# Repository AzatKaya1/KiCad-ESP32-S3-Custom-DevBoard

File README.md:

<div align="center">

# ⚡ ESP32-S3 Custom Development Board

</div>
<div align="center">

<br/>

**A production-grade, 4-layer PCB development board built around the ESP32-S3-WROOM-1 module.**  
Designed for signal integrity, RF performance, and professional-grade hardware standards.

<br/>

</div>

## 📋 Table of Contents

- [Overview](#-overview)
- [Key Features](#-key-features)
- [Technical Specifications](#-technical-specifications)
- [Advanced Hardware Design](#-advanced-hardware-design)
- [PCB Layer Stackup](#-pcb-layer-stackup)
- [Pinout & Peripherals](#-pinout--peripherals)
- [Repository Structure](#-repository-structure)
- [Manufacturing](#-manufacturing)

## 🔍 Overview

This project is an advanced, **production-ready development board** based on the **ESP32-S3-WROOM-1** module. It was designed with a focus on:

- ✅ **Signal Integrity** — Controlled impedance traces, optimized return paths
- ✅ **Power Stability** — Low-noise LDO regulation with proper decoupling
- ✅ **RF Performance** — Dedicated keep-out zone under the module antenna
- ✅ **Professional Standards** — 4-layer stackup, differential pair routing

This board is suitable for makers, engineers, and students who want a reliable ESP32-S3 platform for IoT, wireless communication, sensor integration, or embedded systems development.

## ✨ Key Features

| Feature | Detail |
|---|---|
| 🧠 MCU | ESP32-S3-WROOM-1 — Dual-core Xtensa LX7, Wi-Fi 4 & BLE 5.0 |
| ⚡ USB | Native USB-C for programming and power |
| 🔋 Power | 5V input → 3.3V via AMS1117-3.3 LDO |
| 📡 RF | Keep-out zone for optimized antenna performance |
| 📐 PCB | 4-layer stackup for reduced EMI |
| 🔌 Headers | UART, I2C, SPI — fully broken out |
| 📊 ADC | 2× dedicated analog input channels |
| 🔴 LEDs | Power LED (D1) + User-programmable LED (D2) |
| 🔘 Buttons | RESET (EN) + BOOT (GPIO0) |
| 🧪 Test Points | 5V, 3.3V, GND, TX, RX (TP1–TP5) |

## 🛠 Technical Specifications

| Parameter | Value |
|---|---|
| Microcontroller | ESP32-S3-WROOM-1 |
| CPU | Dual-core Xtensa LX7 @ up to 240 MHz |
| Wireless | Wi-Fi 802.11 b/g/n (2.4 GHz) + BLE 5.0 |
| Flash | Built-in (varies by module variant) |
| Input Voltage | 5V DC via USB-C |
| Operating Voltage | 3.3V (regulated via AMS1117-3.3) |
| PCB Layers | 4 (Signal / GND / Power / Signal) |
| PCB Tool | KiCad 9.0 |
| USB Interface | Native USB (D+/D- differential pair) |
| Programming | USB-C (native), UART via test points |

## 🔬 Advanced Hardware Design

### 1️⃣ 4-Layer PCB & Signal Integrity

The board uses a **4-layer stackup** to deliver superior electrical performance.

By using dedicated internal planes for **GND** and **3.3V**, electromagnetic interference (EMI) is significantly reduced, and power distribution is stabilized across the entire board.

### 2️⃣ Differential Pair Routing (USB D+/D-)

The USB-C data lines are routed as **90-ohm controlled impedance differential pairs**:

- Matched trace lengths for minimal skew
- Consistent spacing to maintain target impedance
- Prevents signal reflection and ensures error-free high-speed data transmission

### 3️⃣ RF Keep-Out Zone

A dedicated **RF Keep-Out Zone** is defined beneath the ESP32-S3-WROOM-1 antenna region:

- No copper, traces, or components on **any layer** in this region
- Maximizes Wi-Fi and Bluetooth range
- Minimizes signal attenuation and multipath interference

### 4️⃣ Power Design — AMS1117-3.3 LDO

The **AMS1117-3.3** was chosen for its:

- Low dropout voltage (~1.2V typical)
- 800mA output current capability
- Excellent noise performance for RF applications
- Wide availability and low cost for prototyping

> ⚠️ **Note:** For battery-powered or low-power designs, consider a more efficient LDO (e.g., MIC5219 or TPS7A20).

### 5️⃣ Decoupling & Bypass Capacitors

- 100nF ceramic capacitors placed close to each power pin of the ESP32-S3 module
- Bulk capacitance at the LDO output for transient response
- Ferrite bead filtering on power input

## 📐 PCB Layer Stackup

| Layer | Type | Description |
|---|---|---|
| Layer 1 (Top) | Signal | Components, USB, buttons, LEDs |
| Layer 2 | GND Plane | Solid ground pour — EMI shield & return path |
| Layer 3 | Power Plane | Solid 3.3V pour — stable power delivery |
| Layer 4 (Bottom) | Signal | Additional routing |

## 🔌 Pinout & Peripherals

| Header | Signals |
|---|---|
| UART | TX, RX, GND, 3.3V |
| I2C | SDA, SCL, GND, 3.3V |
| SPI | MOSI, MISO, SCK, CS, GND, 3.3V |
| ADC | ADC_CH1, ADC_CH2, GND |
| GPIO | Spare GPIO pins for custom expansion |
| Test Points | TP1 = 5V · TP2 = 3.3V · TP3 = GND · TP4 = TX · TP5 = RX |

## 📂 Repository Structure

| Folder / File | Description |
|---|---|
| `Hardware/` | KiCad 9.0 project files (`.kicad_pcb`, `.kicad_sch`, `.kicad_pro`) |
| `Manufacturing/` | Production-ready Gerber, Drill, and POS files |
| `Images/` | High-quality 3D renders |
| `.gitignore` | Git ignore rules |
| `LICENSE` | MIT License |
| `README.md` | This file |

## 🏭 Manufacturing

The `/Manufacturing` folder contains all files needed for PCB fabrication, compatible with major manufacturers:

| Service | Notes |
|---|---|
| [JLCPCB](https://jlcpcb.com) | Recommended — affordable 4-layer PCBs |
| [PCBWay](https://www.pcbway.com) | Good quality, various finish options |
| [OSH Park](https://oshpark.com) | US-based, ENIG finish standard |

**Recommended fab settings:**

| Parameter | Value |
|---|---|
| Layers | 4 |
| PCB Color | Black (recommended) |
| Surface Finish | HASL or ENIG |
| Board Thickness | 1.6mm |
| Copper Weight | 1oz outer / 0.5oz inner |
| Min Trace/Space | 0.15mm |
| Min Hole Size | 0.3mm |

---

<div align="center">

**Designed with  by [Azat KAYA](https://www.linkedin.com/in/azatkaya1/)**

*If this project helped you, consider giving it a ⭐ on GitHub!*

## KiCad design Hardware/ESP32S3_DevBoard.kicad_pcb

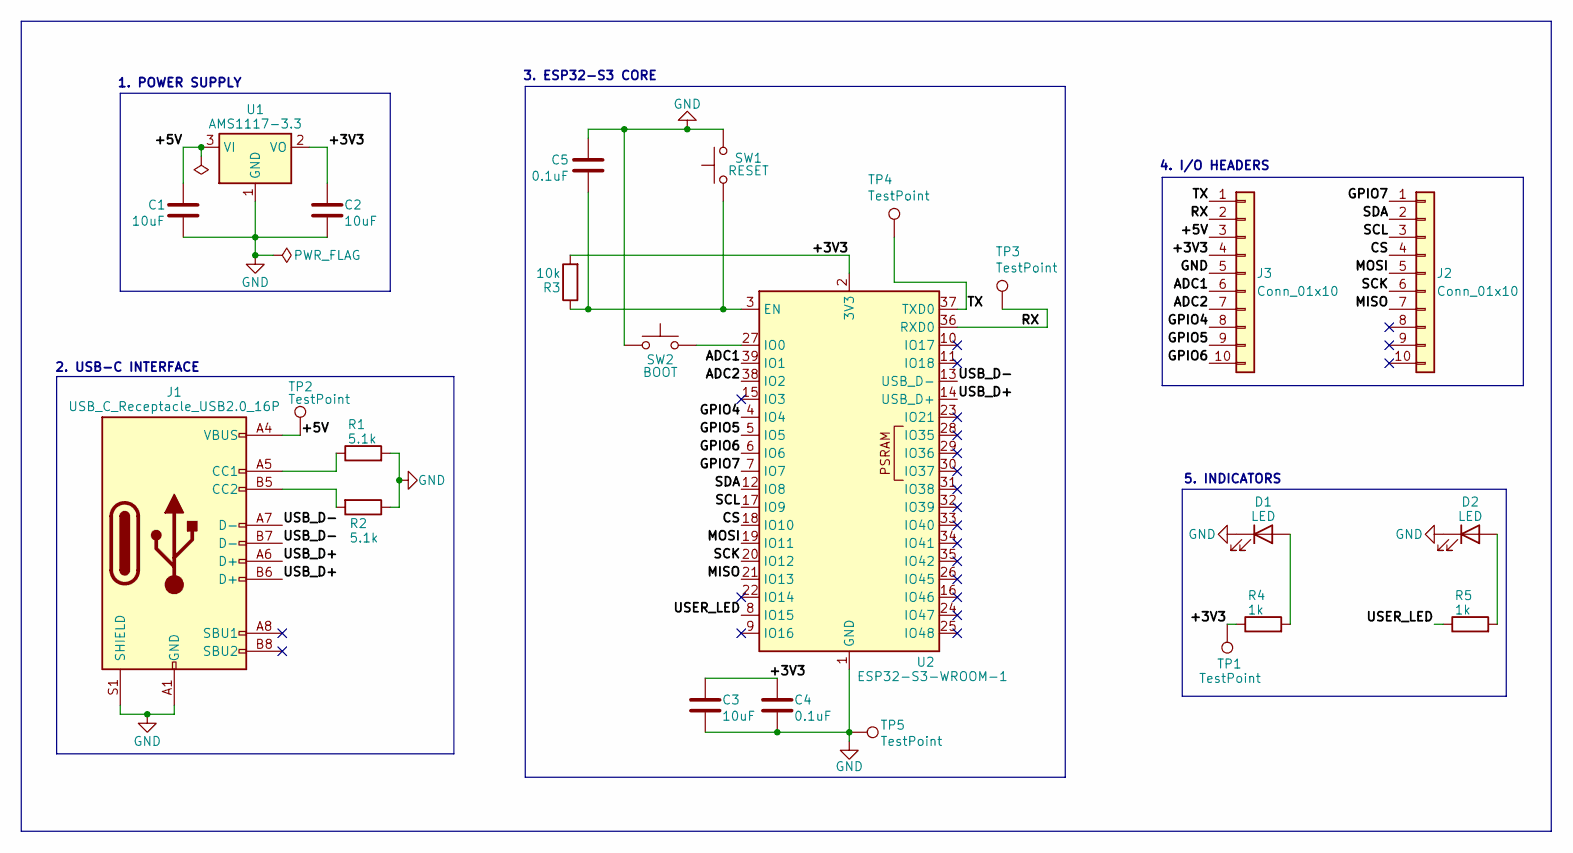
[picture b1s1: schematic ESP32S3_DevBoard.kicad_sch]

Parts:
C1, C2, C3: 10uF; C_0805_2012Metric
C4, C5: 0.1uF; C_0805_2012Metric
D1, D2: LED; LED_0805_2012Metric
J1: USB_C_Receptacle_USB2.0_16P; USB_C_Receptacle_HRO_TYPE-C-31-M-12
J2, J3: Conn_01x10; PinHeader_1x10_P2.54mm_Vertical
R1, R2: 5.1k; R_0805_2012Metric
R3: 10k; R_0805_2012Metric
R4, R5: 1k; R_0805_2012Metric
SW1: RESET; SW_Push_1P1T_NO_E-Switch_TL3301NxxxxxG
SW2: BOOT; SW_Push_1P1T_NO_E-Switch_TL3301NxxxxxG
TP1, TP2, TP3, TP4, TP5: TestPoint; TestPoint_Pad_D1.5mm
U1: AMS1117-3.3; SOT-223-3_TabPin2
U2: ESP32-S3-WROOM-1

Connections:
/+3V3: C2.1, C3.1, C4.1, J3.4, R3.2, R4.1, TP1.1, U1.2 (VO), U2.2 (3V3)
/+5V: C1.1, J1.A4 (VBUS), J1.A9 (VBUS), J1.B4 (VBUS), J1.B9 (VBUS), J3.3, TP2.1, U1.3 (VI)
/ADC1: J3.6, U2.39 (IO1)
/ADC2: J3.7, U2.38 (IO2)
/CS: J2.4, U2.18 (IO10)
/GPIO4: J3.8, U2.4 (IO4)
/GPIO5: J3.9, U2.5 (IO5)
/GPIO6: J3.10, U2.6 (IO6)
/GPIO7: J2.1, U2.7 (IO7)
/MISO: J2.7, U2.21 (IO13)
/MOSI: J2.5, U2.19 (IO11)
/RX: J3.2, TP3.1, U2.36 (RXD0)
/SCK: J2.6, U2.20 (IO12)
/SCL: J2.3, U2.17 (IO9)
/SDA: J2.2, U2.12 (IO8)
/TX: J3.1, TP4.1, U2.37 (TXD0)
/USB_D+: J1.A6 (D+), J1.B6 (D+), U2.14 (USB_D+)
/USB_D-: J1.A7 (D-), J1.B7 (D-), U2.13 (USB_D-)
/USER_LED: R5.1, U2.8 (IO15)
GND: C1.2, C2.2, C3.2, C4.2, C5.1, D1.1 (K), D2.1 (K), J1.A1 (GND), J1.A12 (GND), J1.B1 (GND), J1.B12 (GND), J1.S1 (SHIELD), J3.5, R1.2, R2.1, SW1.2, SW2.1, TP5.1, U1.1 (GND), U2.1 (GND), U2.40 (GND), U2.41 (GND)
unnamed: D1.2 (A), R4.2
unnamed: D2.2 (A), R5.2
unnamed: J1.A5 (CC1), R1.1
unnamed: J1.B5 (CC2), R2.2
unnamed: C5.2, R3.1, SW1.1, U2.3 (EN)
unnamed: SW2.2, U2.27 (IO0)

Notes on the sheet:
3. ESP32-S3 CORE
2. USB-C INTERFACE
5. INDICATORS
1. POWER SUPPLY
4. I/O HEADERS

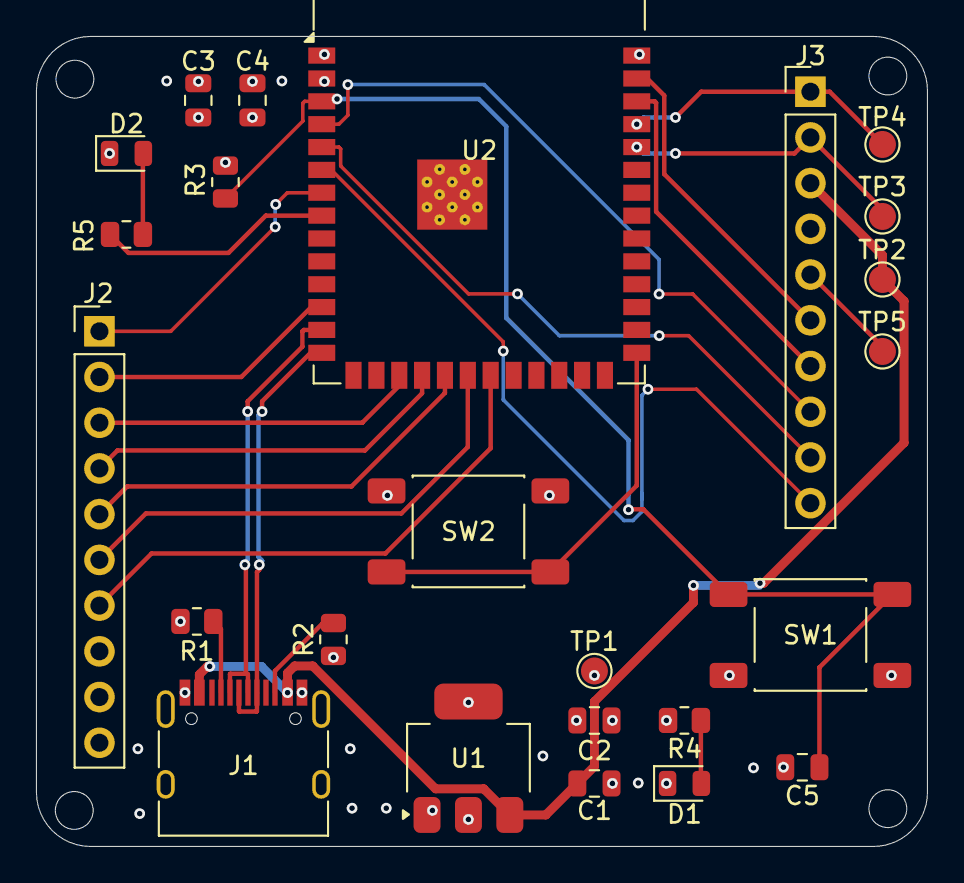
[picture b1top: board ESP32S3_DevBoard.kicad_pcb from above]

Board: 4 copper layers, 49.5 x 45.0 mm, 24 parts (0 on the bottom side), 26 nets.

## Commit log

2026-05-08 Initial manufacturing release
2026-05-09 README.md
